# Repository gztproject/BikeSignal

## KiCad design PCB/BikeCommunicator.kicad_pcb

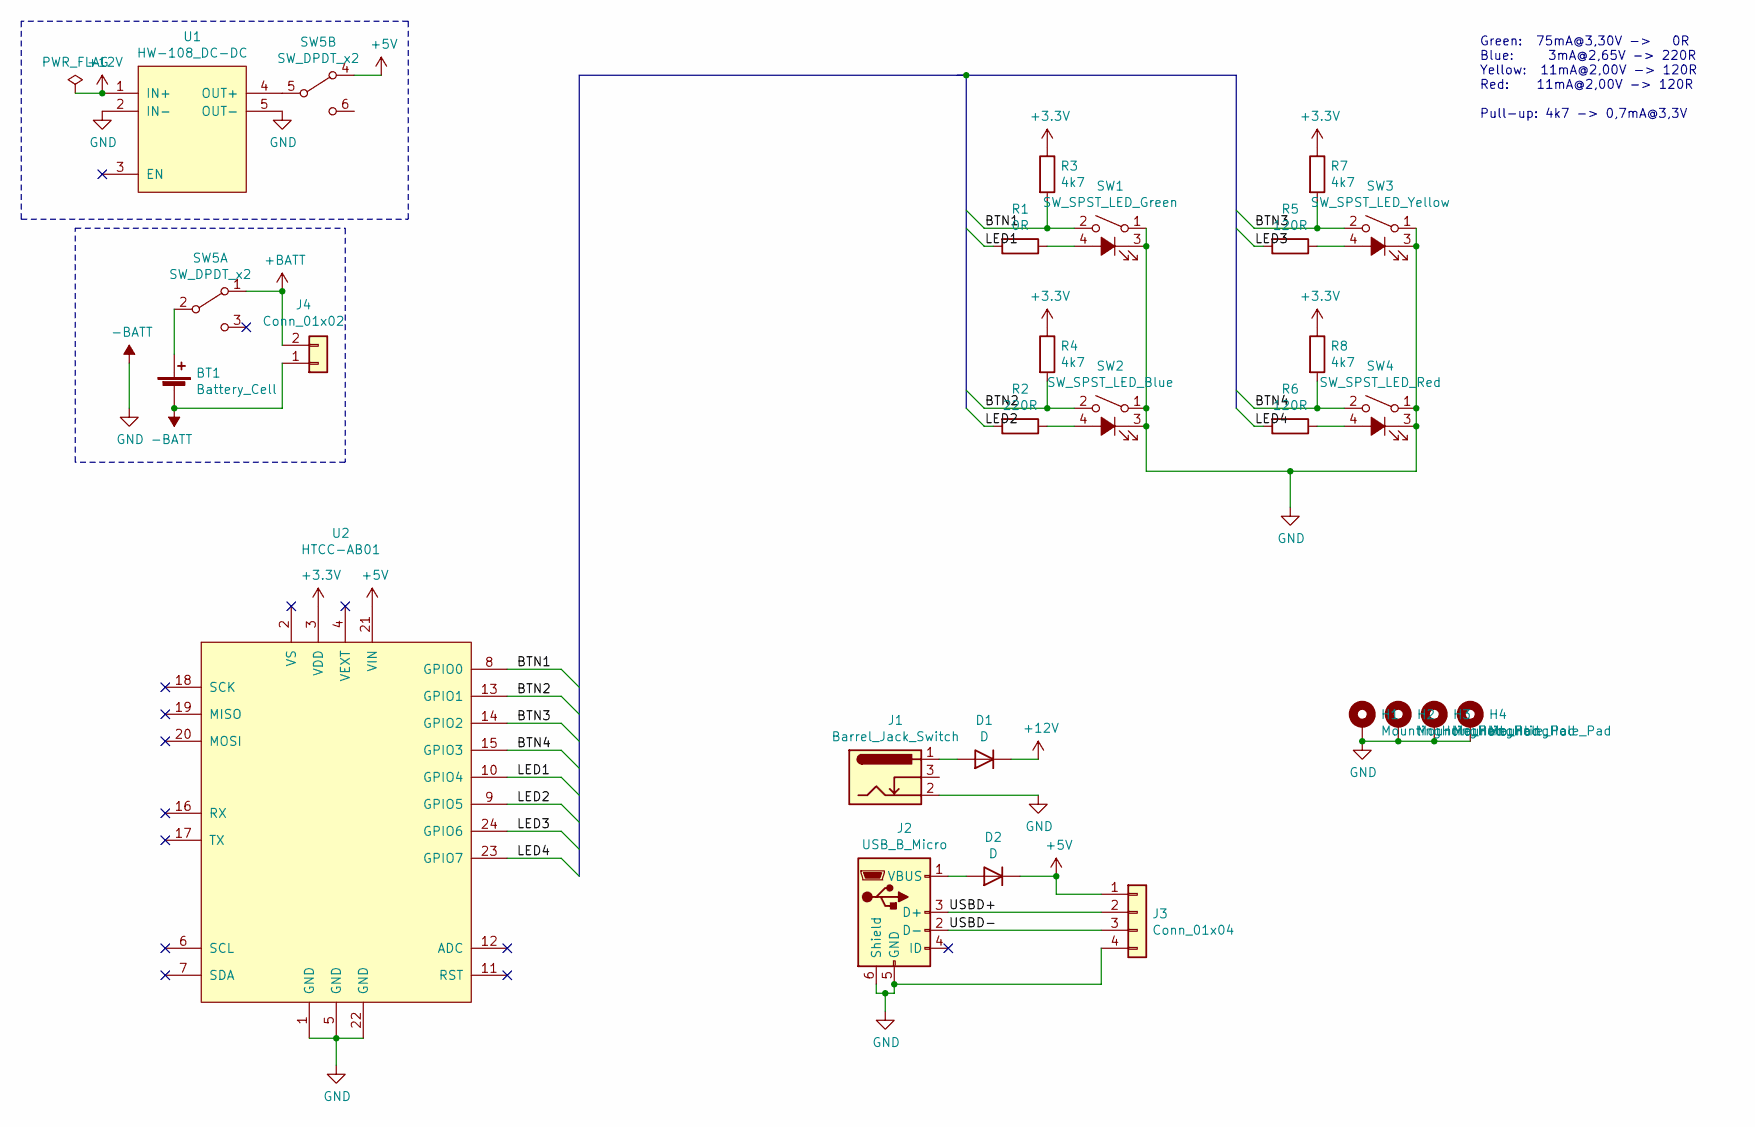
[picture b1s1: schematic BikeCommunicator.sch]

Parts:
BT1: Battery_Cell; SolderWirePad_1x02_P3.81mm_Drill1mm
D1, D2: D; D_SMA
H1, H2, H3, H4: MountingHole_Pad; MountingHole_3.2mm_M3_Pad_Via
J1: Barrel_Jack_Switch; BARREL_JACK
J2: USB_B_Micro; USB_Micro-B_Molex-105017-0001
J3: Conn_01x04; SolderWirePad_1x04_P3.81mm_Drill1mm
J4: Conn_01x02; SolderWirePad_1x02_P3.81mm_Drill1mm
R1: 0R; R_1206
R2: 220R; R_1206
R3, R4, R7, R8: 4k7; R_1206
R5, R6: 120R; R_1206
SW1: SW_SPST_LED_Green; SW_Cherry_MX1A_LED_1.00u_PCB
SW2: SW_SPST_LED_Blue; SW_Cherry_MX1A_LED_1.00u_PCB
SW3: SW_SPST_LED_Yellow; SW_Cherry_MX1A_LED_1.00u_PCB
SW4: SW_SPST_LED_Red; SW_Cherry_MX1A_LED_1.00u_PCB
SW5: SW_DPDT_x2; SW_CuK_JS202011AQN_DPDT_Angled
U1: HW-108_DC-DC; HW-108
U2: HTCC-AB01

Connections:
+3V3: R3.1, R4.1, R7.1, R8.1, U2.3 (VDD)
+5V: D2.1 (K), J3.1, SW5.4 (A), U2.21 (VIN)
+12V: D1.1 (K), U1.1 (IN+)
+BATT: J4.2, SW5.1 (A)
-BATT: BT1.2 (-), H1.1, H2.1, H3.1, H4.1, J1.2, J2.5 (GND), J2.6 (Shield), J3.4, J4.1, SW1.1, SW1.3 (K), SW2.1, SW2.3 (K), SW3.1, SW3.3 (K), SW4.1, SW4.3 (K), U1.2 (IN-), U1.5 (OUT-), U2.1 (GND), U2.5 (GND), U2.22 (GND)
/BTN1: R3.2, SW1.2, U2.8 (GPIO0)
/BTN2: R4.2, SW2.2, U2.13 (GPIO1)
/BTN3: R7.2, SW3.2, U2.14 (GPIO2)
/BTN4: R8.2, SW4.2, U2.15 (GPIO3)
/LED1: R1.2, U2.10 (GPIO4)
/LED2: R2.2, U2.9 (GPIO5)
/LED3: R5.2, U2.24 (GPIO6)
/LED4: R6.2, U2.23 (GPIO7)
/USBD+: J2.3 (D+), J3.2
/USBD-: J2.2 (D-), J3.3
unnamed: BT1.1 (+), SW5.2 (B)
unnamed: D1.2 (A), J1.1
unnamed: D2.2 (A), J2.1 (VBUS)
unnamed: R1.1, SW1.4 (A)
unnamed: R2.1, SW2.4 (A)
unnamed: R5.1, SW3.4 (A)
unnamed: R6.1, SW4.4 (A)
unnamed: SW5.5 (B), U1.4 (OUT+)

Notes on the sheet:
Green: 75mA@3,30V -> 0R Blue: 3mA@2,65V -> 220R Yellow: 11mA@2,00V -> 120R Red: 11mA@2,00V -> 120R Pull-up: 4k7 -> 0,7mA@3,3V

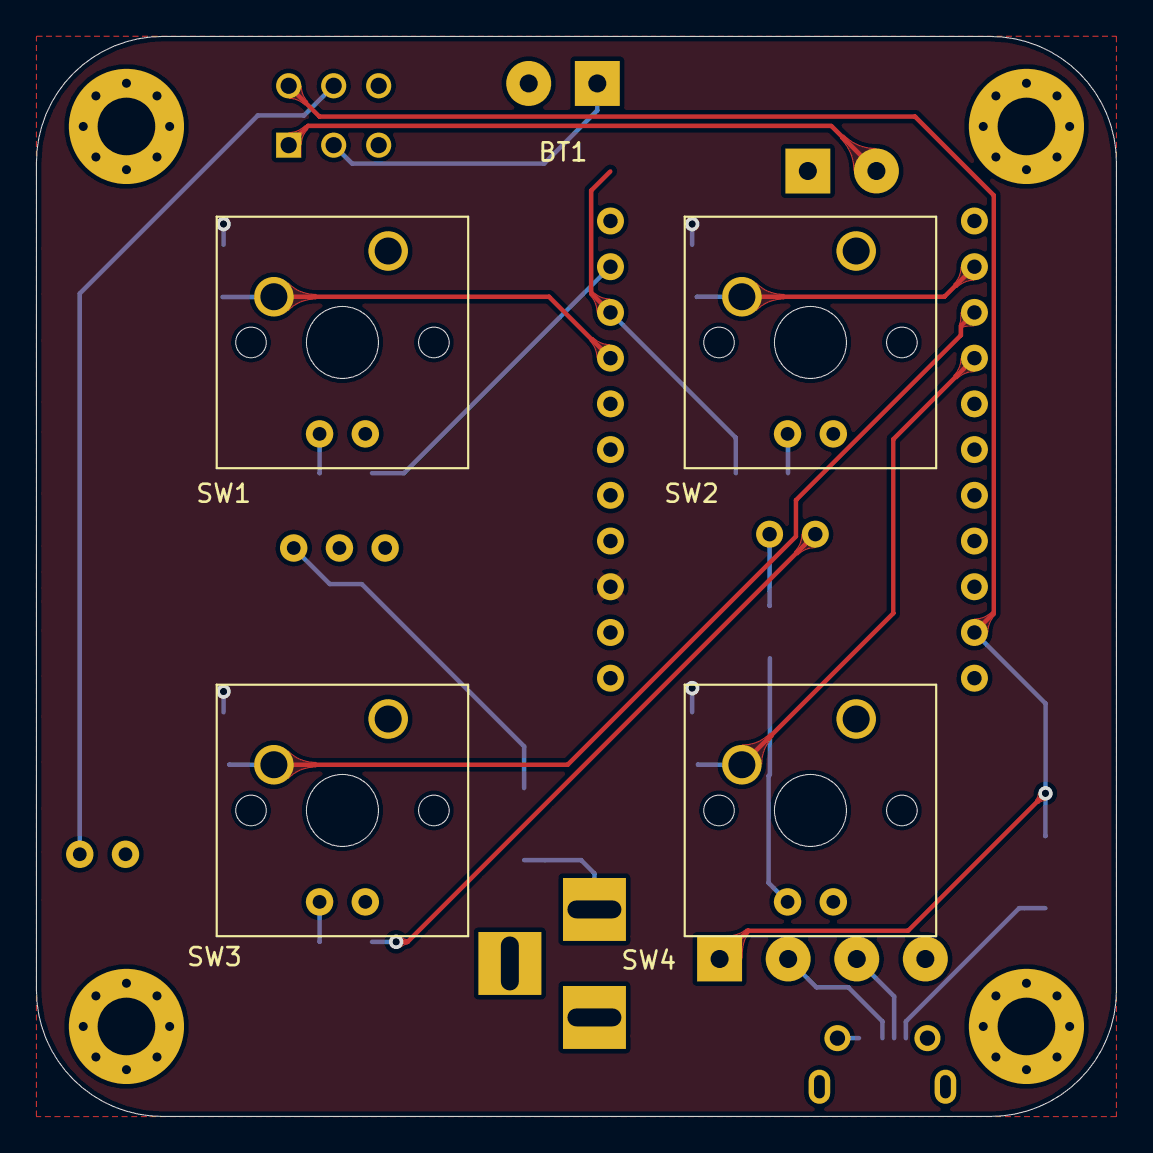
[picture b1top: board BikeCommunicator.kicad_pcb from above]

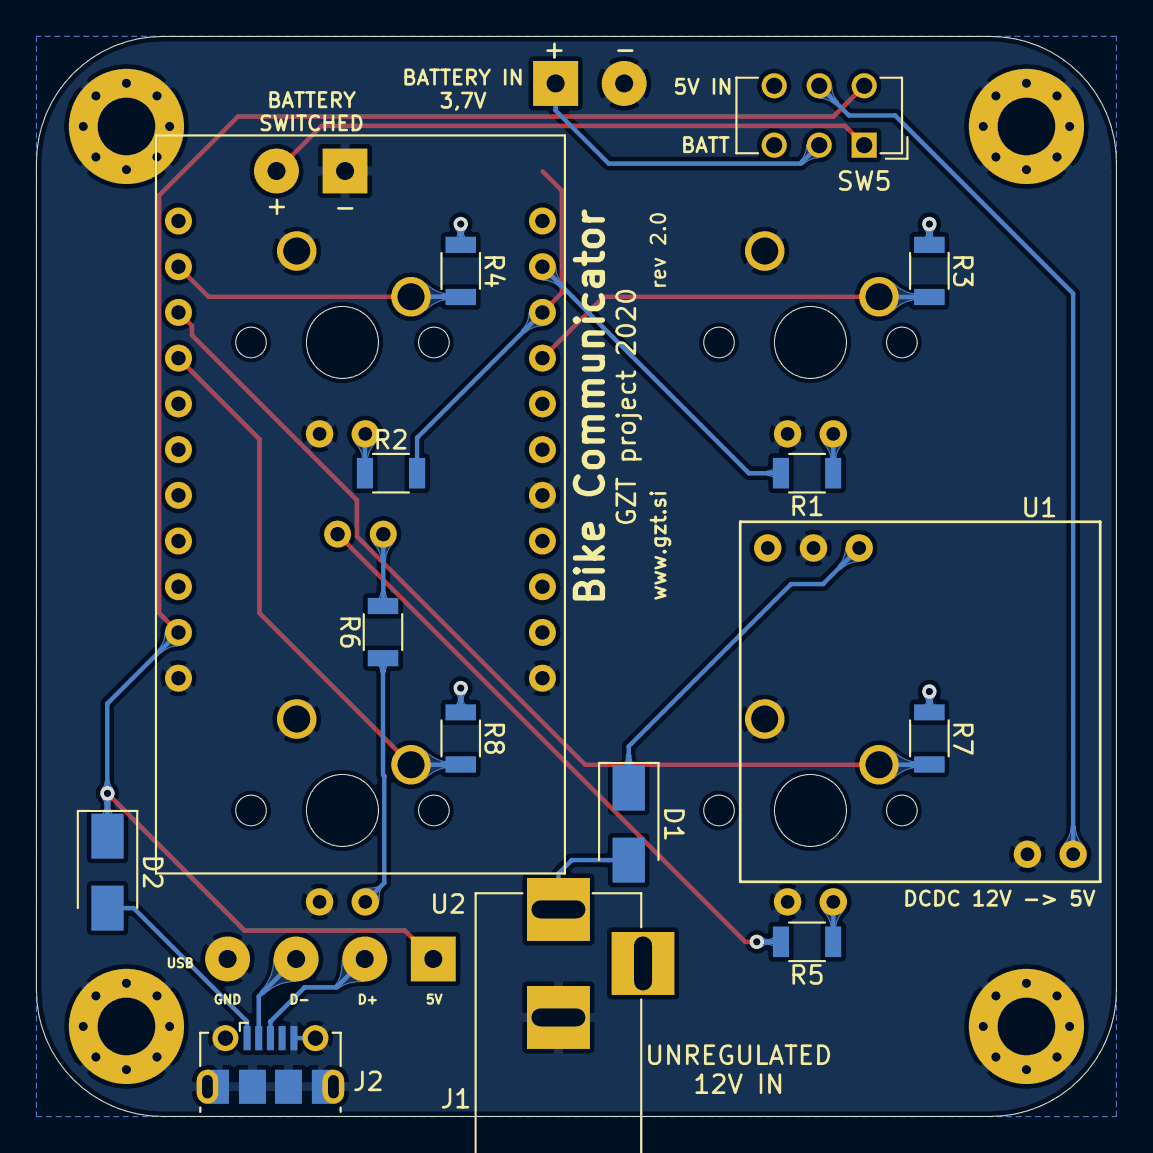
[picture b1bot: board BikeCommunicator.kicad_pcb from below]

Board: 2 copper layers, 60.0 x 60.0 mm, 26 parts (16 on the bottom side), 23 nets.

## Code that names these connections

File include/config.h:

#define BTN1PIN GPIO0
#define BTN2PIN GPIO1
#define BTN3PIN GPIO2
#define BTN4PIN GPIO3

#define BTN1LED GPIO4
#define BTN2LED GPIO5
#define BTN3LED GPIO6
#define BTN4LED GPIO7

#define LED_LOW_INT 0
#define LED_HIGH_INT 255

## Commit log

2020-06-09 Added existing files
2020-06-09 Fixed various errors.
2020-06-09 Fixed more bugs
2020-06-09 Added build test
2020-06-09 Added panel support for 4 buttons and LEDs
2020-06-09 More bugfixes
2020-06-10 Bugfixes
2020-06-10 Added some more LED indications
2020-06-10 Fit PCB to housing, added some more elements to scheme
2020-06-11 Redesigned PCB and housing to fit it.
2020-06-11 Updated gerbers
2020-06-12 Added Slicer file and PDF
2020-06-13 Added resistor values
2020-06-13 A few more bugfixes
2020-06-14 Updated PCB project file
2020-06-14 Updated the housing models
2020-06-14 Added more covers
2020-06-19 Create LICENSE
2020-08-14 Major PCB fix
2020-11-04 SMD components on PCB, fabrication files...
